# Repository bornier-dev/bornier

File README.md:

# Bornier

Open source EtherCAT slaves for machine tools running LinuxCNC: hardware, firmware and tooling.

- Website: [bornier.dev](https://bornier.dev)

> **Status: board bring-up.** Nothing here is usable yet. The first base boards are built and
> are being brought up block by block: the firmware runs on them and has on-target tests for
> the blocks checked so far, without the EtherCAT stack yet.

## Goals

- A family of standard-compliant EtherCAT slaves for CNC retrofits: motion (step/dir, encoders, probe), digital and analog I/O, spindle control, Modbus gateway.
- Works with any EtherCAT master; developed and tested against LinuxCNC with the IgH master (`lcec`).
- Firmware builds on the LinuxCNC PC itself with a free toolchain (`arm-none-eabi-gcc`, CMake) and updates over EtherCAT (FoE).
- Hardware designed in KiCad, published in full.

Out of scope: functional safety. E-stop and STO stay hardwired.

## Architecture

```
          EtherCAT (daisy chain)
LinuxCNC PC ──► [Base board A] ──► [EtherCAT drive] ──► [Base board B] ──► ...
 (IgH master)        │ HE10 ribbon (local bus, not EtherCAT)
                     ├── I/O module 1
                     └── I/O module n
```

- **One generic base board** per EtherCAT slave. More axes come from more boards on the
  EtherCAT chain (8 axes with two boards, 12 with three).
- **Extension modules** on DIN rail, chained to the base board by HE10 ribbons: slow I/O on SPI
  chips, without an MCU. A base board and its modules form a single modular slave.

## Base board

Schematic and PCB in [`hardware/base/`](hardware/base), generated by script (see below); the PCB is
being placed.

| Block | Content |
|---|---|
| Core | Microchip LAN9253 EtherCAT slave controller (two ports, RJ45 with magnetics), STM32H523 MCU in LQFP-100 over SPI/OCTOSPI, one shared 25 MHz MEMS oscillator |
| Power | 12 V or 24 V logic supply (10.8–30 V): fuse, TVS, reverse polarity protection, bucks to 5 V and 3.3 V; USB micro-B for bench power and DFU flashing |
| Motion | 4 axes, each on a dual RJ45: drive port (differential step/dir, enable, alarm, current-limited supply output) and encoder port (RS-422, TTL or HTL, 5 V or supply voltage); fast probe input |
| Spindle | 0-10 V speed reference, PWM, enable and direction |
| Modbus | Isolated RS-485, switchable termination |
| Safety | E-stop state input (wired, not a safety function), external watchdog on the MCU reset |
| Local bus | HE10 2 × 17 connector to the extension modules: SPI, 12 chip selects, I²C, IRQ, LATCH, OE |

The STM32H523 footprint takes any STM32H5 in LQFP-100 (H523, H533, H562, H563) without a PCB
change. The board is meant to be fed by a dedicated supply in the same cabinet; the
simulation of the input stage and its limits is in [`hardware/base/sim/`](hardware/base/sim/README.md).

The board is 107.5 × 150 mm. It mounts on a DIN rail in a Phoenix Contact UM-BASIC 108 profile
(housing kit UM-BASIC-KIT-B108-L150-7035), resting on the profile walls at the top level, or
screws onto a panel through four M3 holes at the corners, one of them plated to earth the board.
A plated hole takes the Phoenix PE contact, which earths the board to the DIN rail. Every edge
connector sits on a long edge: the profile closes the short ones; the USB jack is vertical.

## Repository layout

| Directory | Contents |
|---|---|
| [`firmware/`](firmware/README.md) | C++23 firmware on the [OpSy](https://github.com/Otatiaro/OpSy) RTOS, generated STM32H523 register headers, board support for the base board, bring-up examples and on-target tests |
| `hardware/lib/` | `kicadgen`, the Python schematic generator and checker (ERC, netlist), and the symbols, footprints and 3D models missing from the KiCad libraries, with their generators |
| `hardware/base/` | Base board: schematic generator (`gen/`), KiCad project (`kicad/`), Gerbers (`fab/`), circuit simulation (`sim/`) |
| [`tools/hil/`](tools/hil/README.md) | Hardware-in-the-loop test scripts |
| `tools/udev/` | udev rules for debug probes on Linux |

The schematic is generated: edit the scripts in `hardware/base/gen/`, then run
`python hardware/base/gen/schematic.py`, which regenerates it and runs the checks. The PCB is edited in
KiCad: after a schematic change, update it from the schematic (Tools > Update PCB from Schematic).

Building, flashing and coding rules: [CONTRIBUTING.md](CONTRIBUTING.md).

## Licensing

| Part | License |
|---|---|
| Hardware (KiCad projects) | [CERN-OHL-W-2.0](LICENSES/CERN-OHL-W-2.0.txt) |
| Firmware and tools | [MPL-2.0](LICENSES/MPL-2.0.txt) |
| Documentation | [CC-BY-4.0](LICENSES/CC-BY-4.0.txt) |

Each file carries an SPDX header naming its license.

## Official builds and forks

Official releases will carry the Bornier EtherCAT Vendor ID. Forks distributing hardware or firmware must use their own Vendor ID.

EtherCAT® is a registered trademark and patented technology, licensed by Beckhoff Automation GmbH, Germany.

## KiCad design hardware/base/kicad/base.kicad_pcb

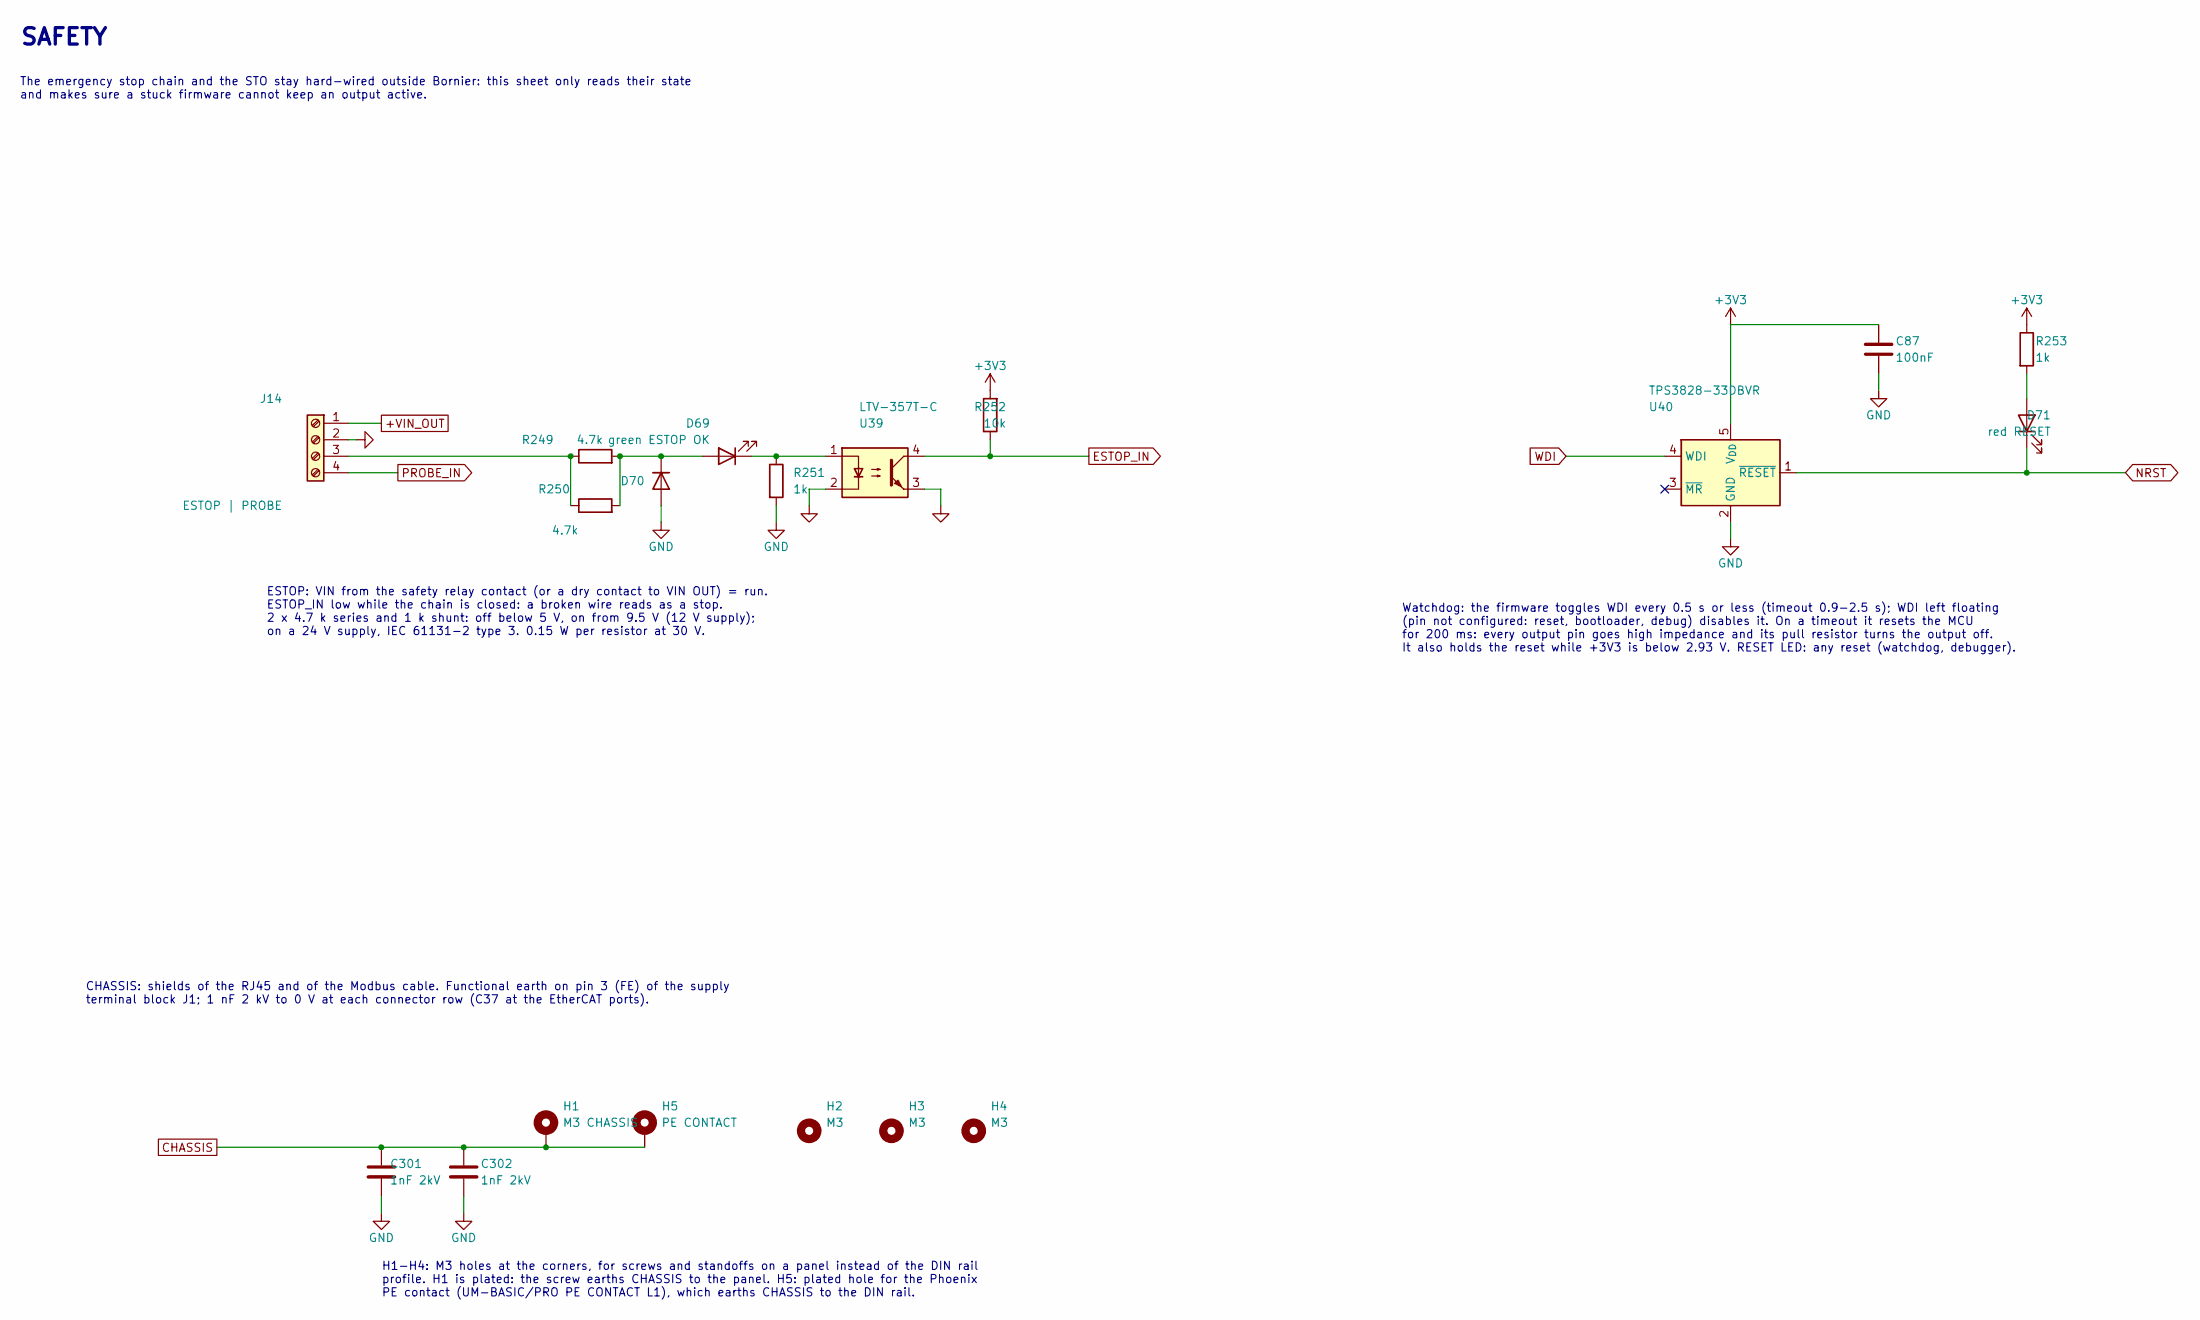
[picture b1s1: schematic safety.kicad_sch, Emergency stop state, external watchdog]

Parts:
C87: 100nF; C_0402_1005Metric; LCSC C307331
C301, C302: 1nF 2kV; C_1206_3216Metric; LCSC C9196
D69: green ESTOP OK; LED_0603_1608Metric; LCSC C2289
D70: 1N4148WS; D_SOD-323; LCSC C2128
D71: red RESET; LED_0603_1608Metric; LCSC C2286
H1: M3 CHASSIS; MountingHole_3.2mm_M3_Pad
H2, H3, H4: M3; MountingHole_3.2mm_M3
H5: PE CONTACT; MountingHole_3.2mm_M3_Pad
J14: ESTOP | PROBE; PhoenixContact_MC_1,5_4-G-3.81_1x04_P3.81mm_Horizontal; LCSC C441184
R249, R250: 4.7k; R_1206_3216Metric; LCSC C17936
R251, R253: 1k; R_0402_1005Metric; LCSC C11702
R252: 10k; R_0402_1005Metric; LCSC C25744
U39: LTV-357T-C; SO-4_4.4x3.6mm_P2.54mm; LCSC C119091
U40: TPS3828-33DBVR; SOT-23-5; LCSC C20032

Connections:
+3V3: C87.1, R252.2, R253.1, U40.5 (V_{DD}); also elsewhere on the board
+VIN_OUT: J14.1; also elsewhere on the board
CHASSIS: C301.1, C302.1, H1.1, H5.1; also elsewhere on the board
ESTOP_IN: R252.1, U39.4; also elsewhere on the board
GND: C87.2, C301.2, C302.2, D70.2 (A), J14.2, R251.2, U39.2, U39.3, U40.2 (GND); also elsewhere on the board
NRST: D71.1 (K), U40.1 (~RESET); also elsewhere on the board
unnamed: D69.2 (A), D70.1 (K), R249.2, R250.2
unnamed: D69.1 (K), R251.1, U39.1
unnamed: D71.2 (A), R253.2
unnamed: J14.3, R249.1, R250.1
PROBE_IN: J14.4; also elsewhere on the board
WDI: U40.4 (WDI); also elsewhere on the board

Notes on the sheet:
SAFETY
The emergency stop chain and the STO stay hard-wired outside Bornier: this sheet only reads their state and makes sure a stuck firmware cannot keep an output active.
ESTOP: VIN from the safety relay contact (or a dry contact to VIN OUT) = run. ESTOP_IN low while the chain is closed: a broken wire reads as a stop. 2 x 4.7 k series and 1 k shunt: off below 5 V, on from 9.5 V (12 V supply); on a 24 V supply, IEC 61131-2 type 3. 0.15 W per resistor at 30 V.
Watchdog: the firmware toggles WDI every 0.5 s or less (timeout 0.9-2.5 s); WDI left floating (pin not configured: reset, bootloader, debug) disables it. On a timeout it resets the MCU for 200 ms: every output pin goes high impedance and its pull resistor turns the output off. It also holds the res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
CHASSIS: shields of the RJ45 and of the Modbus cable. Functional earth on pin 3 (FE) of the supply terminal block J1; 1 nF 2 kV to 0 V at each connector row (C37 at the EtherCAT ports).
H1-H4: M3 holes at the corners, for screws and standoffs on a panel instead of the DIN rail profile. H1 is plated: the screw earths CHASSIS to the panel. H5: plated hole for the Phoenix PE contact (UM-BASIC/PRO PE CONTACT L1), which earths CHASSIS to the DIN rail.

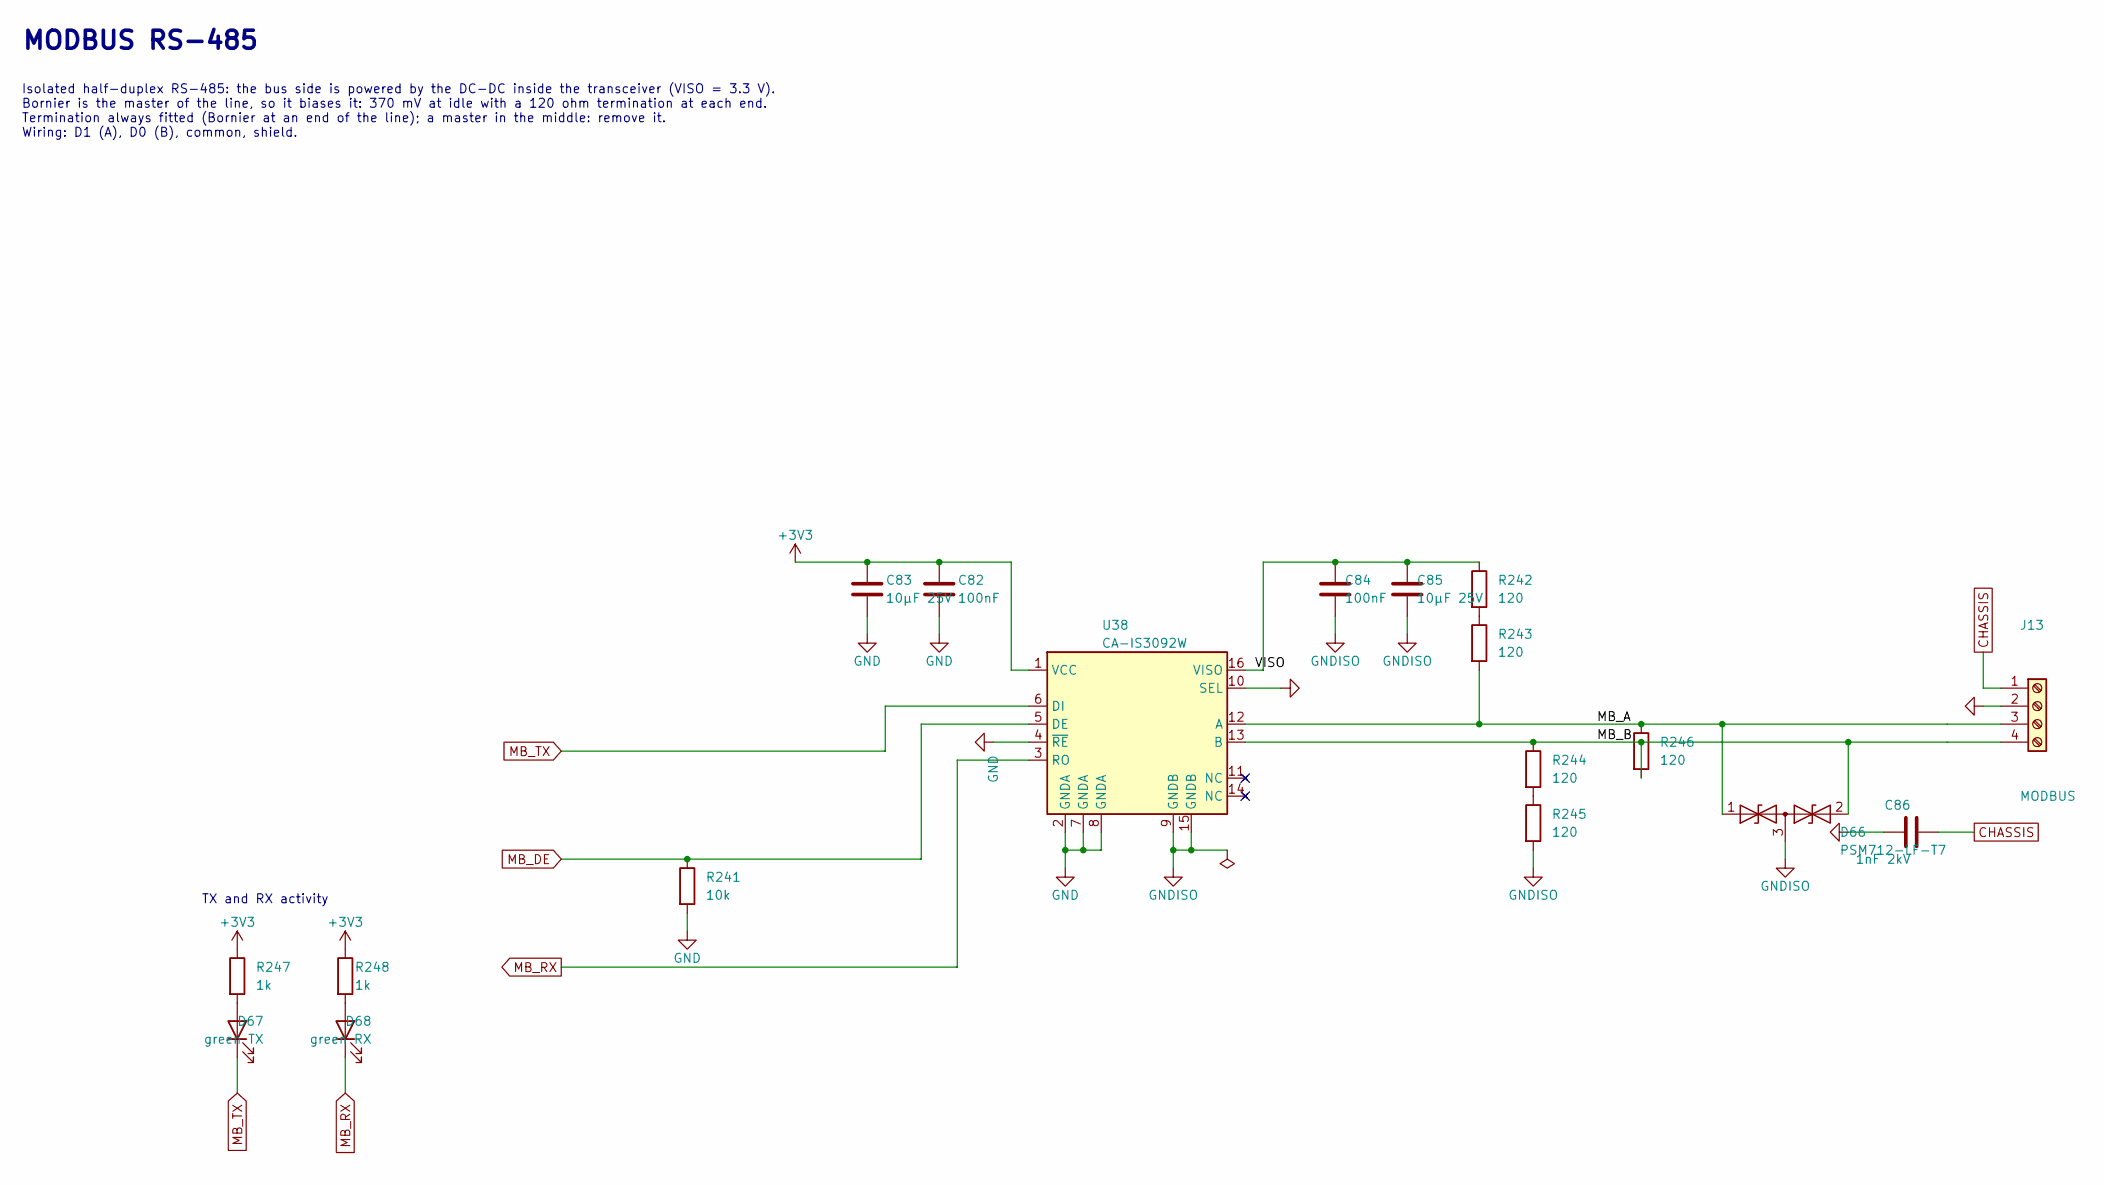
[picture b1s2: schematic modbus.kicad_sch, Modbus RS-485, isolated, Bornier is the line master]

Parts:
C82, C84: 100nF; C_0402_1005Metric; LCSC C307331
C83, C85: 10µF 25V; C_0805_2012Metric; LCSC C15850
C86: 1nF 2kV; C_1206_3216Metric; LCSC C9196
D66: PSM712-LF-T7; SOT-23; LCSC C32677
D67: green TX; LED_0603_1608Metric; LCSC C2289
D68: green RX; LED_0603_1608Metric; LCSC C2289
J13: MODBUS; PhoenixContact_MC_1,5_4-G-3.81_1x04_P3.81mm_Horizontal; LCSC C441184
R241: 10k; R_0402_1005Metric; LCSC C25744
R242, R243, R244, R245, R246: 120; R_0603_1608Metric; LCSC C22787
R247, R248: 1k; R_0402_1005Metric; LCSC C11702
U38: CA-IS3092W; SOIC-16W_7.5x10.3mm_P1.27mm; LCSC C2890051

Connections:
+3V3: C82.1, C83.1, R247.1, R248.1, U38.1 (VCC); also elsewhere on the board
/Modbus/MB_A: D66.1 (A1), J13.3, R243.2, R246.1, U38.12 (A)
/Modbus/MB_B: D66.2 (A2), J13.4, R244.1, R246.2, U38.13 (B)
/Modbus/VISO: C84.1, C85.1, R242.1, U38.16 (VISO)
CHASSIS: C86.2, J13.1; also elsewhere on the board
GND: C82.2, C83.2, R241.2, U38.2 (GNDA), U38.4 (~RE), U38.7 (GNDA), U38.8 (GNDA); also elsewhere on the board
GNDISO: C84.2, C85.2, C86.1, D66.3 (common), J13.2, R245.2, U38.9 (GNDB), U38.10 (SEL), U38.15 (GNDB)
MB_DE: R241.1, U38.5 (DE); also elsewhere on the board
MB_RX: D68.1 (K), U38.3 (RO); also elsewhere on the board
MB_TX: D67.1 (K), U38.6 (DI); also elsewhere on the board
unnamed: D67.2 (A), R247.2
unnamed: D68.2 (A), R248.2
unnamed: R242.2, R243.1
unnamed: R244.2, R245.1

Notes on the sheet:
MODBUS RS-485
Isolated half-duplex RS-485: the bus side is powered by the DC-DC inside the transceiver (VISO = 3.3 V). Bornier is the master of the line, so it biases it: 370 mV at idle with a 120 ohm termination at each end. Termination always fitted (Bornier at an end of the line); a master in the middle: remo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
TX and RX activity

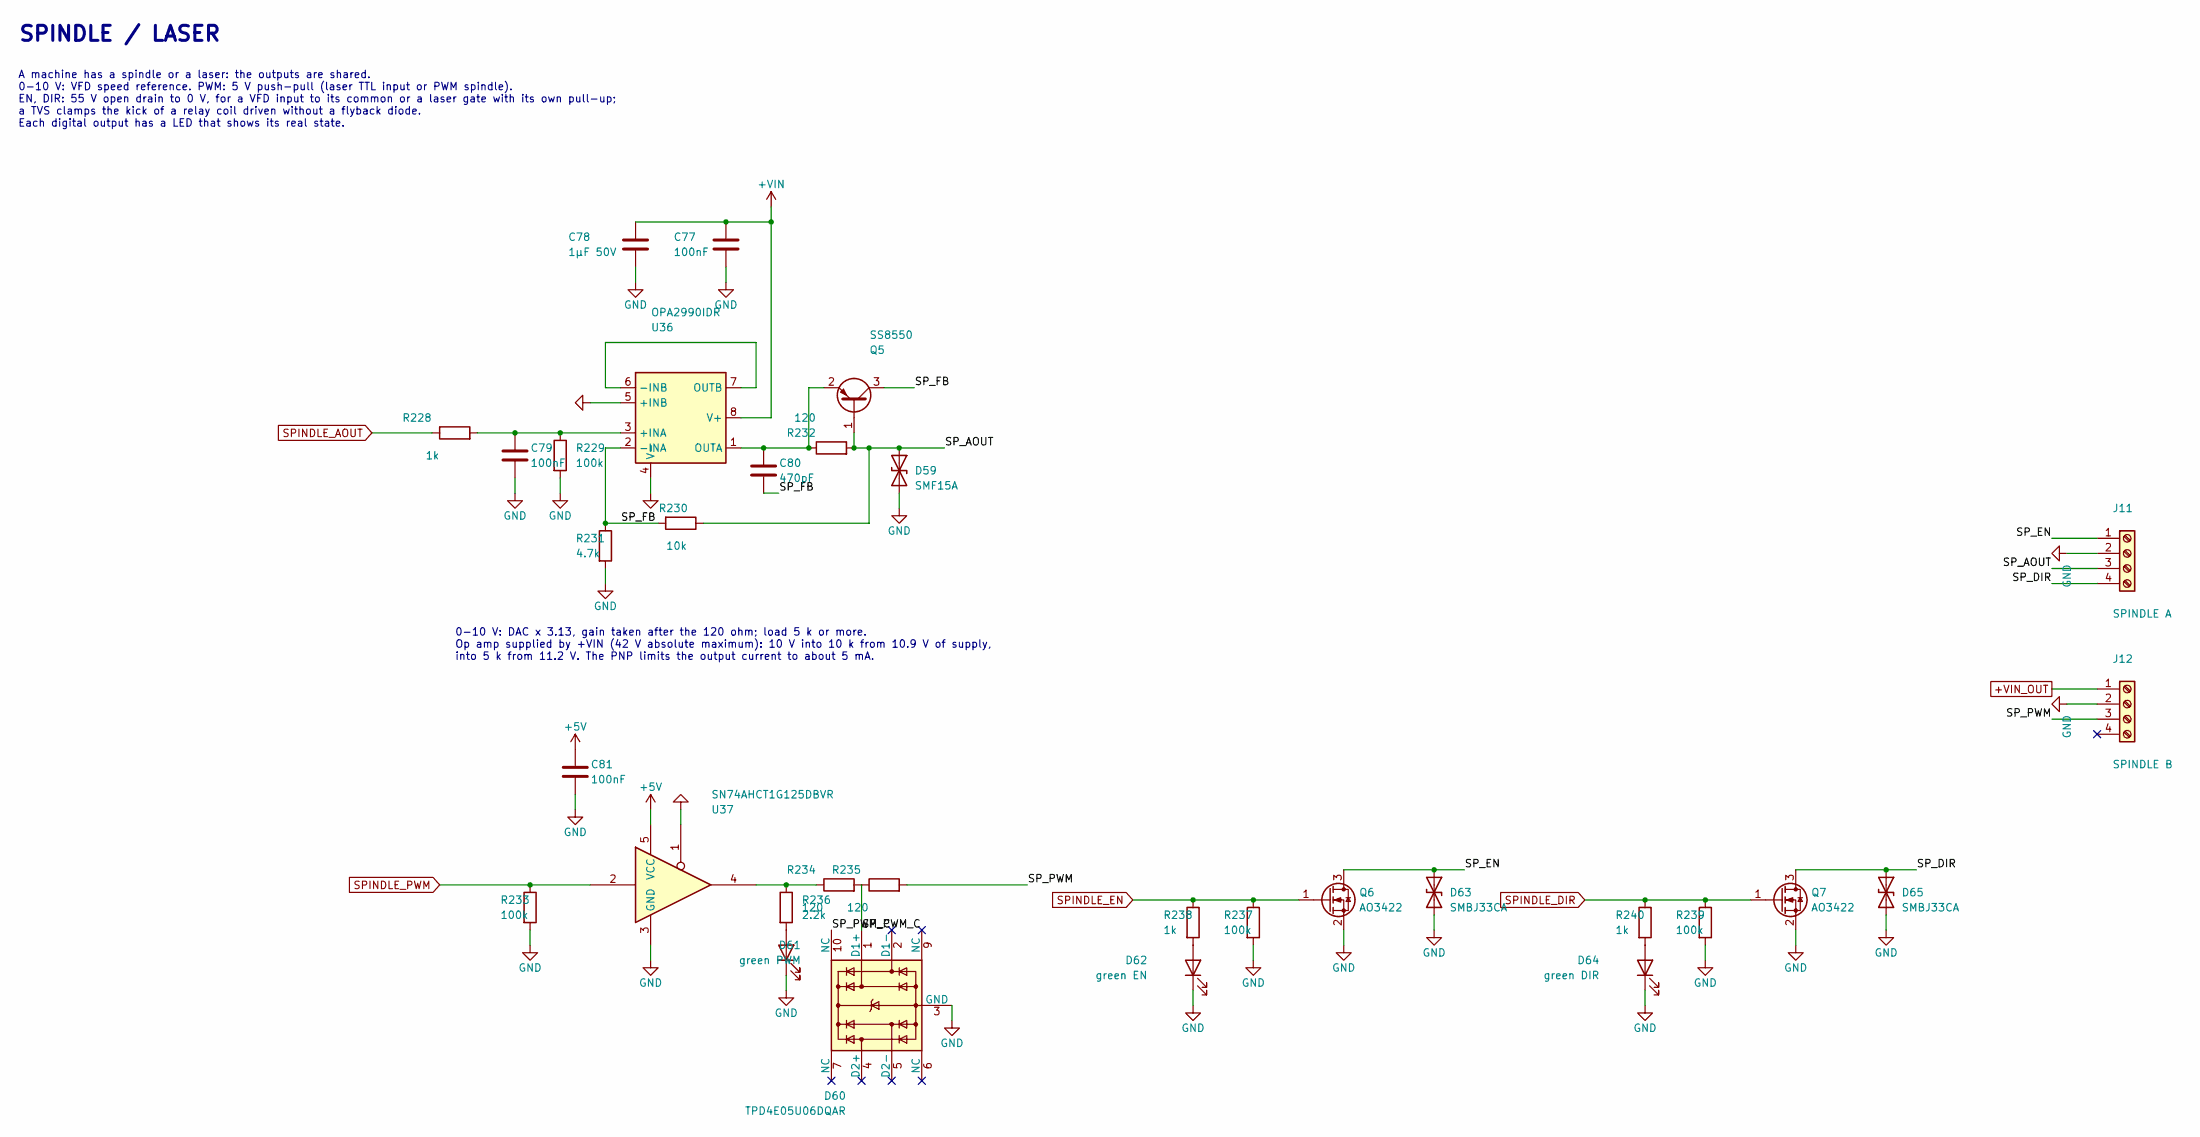
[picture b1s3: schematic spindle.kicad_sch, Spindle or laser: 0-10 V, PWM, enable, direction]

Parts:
C77, C79, C81: 100nF; C_0402_1005Metric; LCSC C307331
C78: 1µF 50V; C_0603_1608Metric; LCSC C15849
C80: 470pF; C_0402_1005Metric; LCSC C1537
D59: SMF15A; D_SOD-123F; LCSC C123802
D60: TPD4E05U06DQAR; USON-10_2.5x1.0mm_P0.5mm; LCSC C138714
D61: green PWM; LED_0603_1608Metric; LCSC C2289
D62: green EN; LED_0603_1608Metric; LCSC C2289
D63, D65: SMBJ33CA; D_SMB; LCSC C78420
D64: green DIR; LED_0603_1608Metric; LCSC C2289
J11: SPINDLE A; PhoenixContact_MC_1,5_4-G-3.81_1x04_P3.81mm_Horizontal; LCSC C441184
J12: SPINDLE B; PhoenixContact_MC_1,5_4-G-3.81_1x04_P3.81mm_Horizontal; LCSC C441184
Q5: SS8550; SOT-23; LCSC C8542
Q6, Q7: AO3422; SOT-23; LCSC C37130
R228, R238, R240: 1k; R_0402_1005Metric; LCSC C11702
R229, R233, R237, R239: 100k; R_0402_1005Metric; LCSC C25741
R230: 10k; R_0402_1005Metric; LCSC C25744
R231: 4.7k; R_0402_1005Metric; LCSC C25900
R232, R234, R235: 120; R_0603_1608Metric; LCSC C22787
R236: 2.2k; R_0402_1005Metric; LCSC C25879
U36: OPA2990IDR; SOIC-8_3.9x4.9mm_P1.27mm; LCSC C2058283
U37: SN74AHCT1G125DBVR; SOT-23-5; LCSC C7484

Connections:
+5V: C81.1, U37.5 (VCC); also elsewhere on the board
+VIN: C77.1, C78.1, U36.8 (V+); also elsewhere on the board
+VIN_OUT: J12.1; also elsewhere on the board
/Spindle/SP_AOUT: D59.1 (A1), J11.3, Q5.1 (B), R230.1, R232.2
/Spindle/SP_DIR: D65.1 (A1), J11.4, Q7.3 (D)
/Spindle/SP_EN: D63.1 (A1), J11.1, Q6.3 (D)
/Spindle/SP_FB: C80.2, Q5.3 (C), R230.2, R231.1, U36.2 (-INA)
/Spindle/SP_PWM: J12.3, R235.2
/Spindle/SP_PWM_C: D60.1 (D1+), D60.10 (NC), R234.2, R235.1
GND: C77.2, C78.2, C79.2, C81.2, D59.2 (A2), D60.3 (GND), D60.8 (GND), D61.1 (K), D62.1 (K), D63.2 (A2), D64.1 (K), D65.2 (A2), J11.2, J12.2, Q6.2 (S), Q7.2 (S), R229.2, R231.2, R233.2, R237.2, R239.2, U36.4 (V-), U36.5 (+INB), U37.1, U37.3 (GND); also elsewhere on the board
unnamed: D61.2 (A), R236.2
unnamed: D62.2 (A), R238.2
unnamed: D64.2 (A), R240.2
unnamed: C80.1, Q5.2 (E), R232.1, U36.1 (OUTA)
unnamed: R234.1, R236.1, U37.4
unnamed: C79.1, R228.2, R229.1, U36.3 (+INA)
unnamed: U36.6 (-INB), U36.7 (OUTB)
SPINDLE_AOUT: R228.1; also elsewhere on the board
SPINDLE_DIR: Q7.1 (G), R239.1, R240.1; also elsewhere on the board
SPINDLE_EN: Q6.1 (G), R237.1, R238.1; also elsewhere on the board
SPINDLE_PWM: R233.1, U37.2; also elsewhere on the board

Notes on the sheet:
SPINDLE / LASER
A machine has a spindle or a laser: the outputs are shared. 0-10 V: VFD speed reference. PWM: 5 V push-pull (laser TTL input or PWM spindle). EN, DIR: 55 V open drain to 0 V, for a VFD input to its common or a laser gate with its own pull-up; a TVS clamps the kick of a relay coil driven without a f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
0-10 V: DAC x 3.13, gain taken after the 120 ohm; load 5 k or more. Op amp supplied by +VIN (42 V absolute maximum): 10 V into 10 k from 10.9 V of supply, into 5 k from 11.2 V. The PNP limits the output current to about 5 mA.

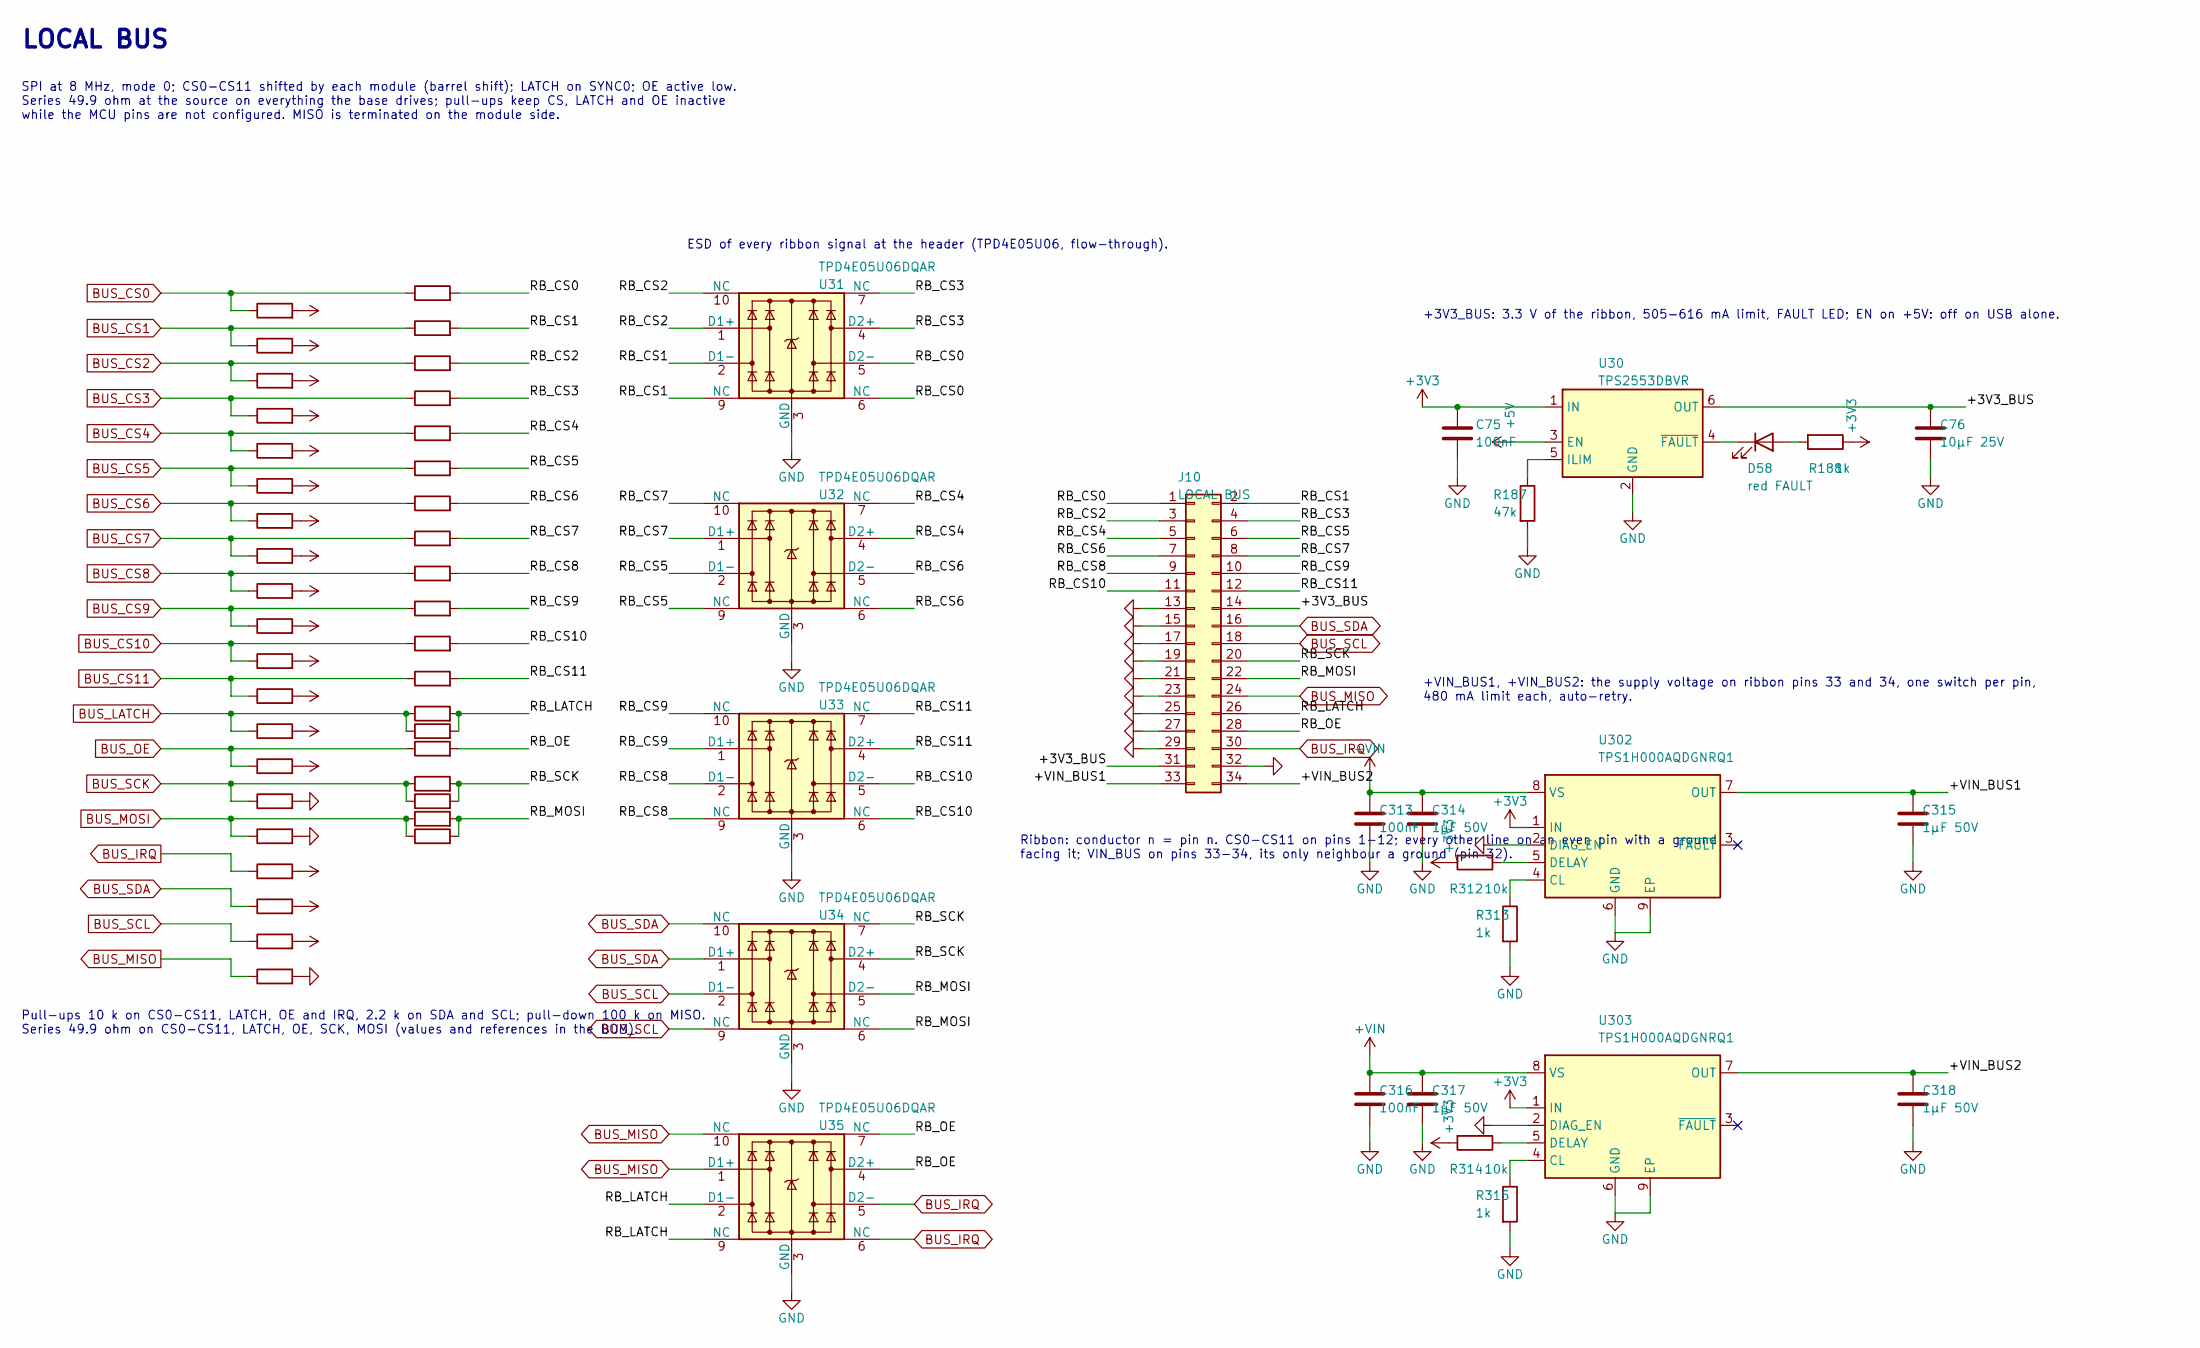
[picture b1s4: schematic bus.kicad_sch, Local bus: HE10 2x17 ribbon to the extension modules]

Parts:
C75, C313, C316: 100nF; C_0402_1005Metric; LCSC C307331
C76: 10µF 25V; C_0805_2012Metric; LCSC C15850
C314, C315, C317, C318: 1µF 50V; C_0603_1608Metric; LCSC C15849
D58: red FAULT; LED_0603_1608Metric; LCSC C2286
J10: LOCAL BUS; IDC-Header_2x17_P2.54mm_Vertical; LCSC C20920
R187: 47k; R_0402_1005Metric; LCSC C25792
R188, R313, R315: 1k; R_0402_1005Metric; LCSC C11702
R189, R190, R191, R192, R193, R194, R195, R196, R197, R198, R199, R200, R201, R202, R222, R312, R314: 10k; R_0402_1005Metric; LCSC C25744
R203, R204, R205, R206, R207, R208, R209, R210, R211, R212, R213, R214, R215, R216, R217, R218, R219, R220, R221: 49.9; R_0603_1608Metric; LCSC C23185
R223, R224, R225: 100k; R_0402_1005Metric; LCSC C25741
R226, R227: 2.2k; R_0402_1005Metric; LCSC C25879
U30: TPS2553DBVR; SOT-23-6; LCSC C55266
U31, U32, U33, U34, U35: TPD4E05U06DQAR; USON-10_2.5x1.0mm_P0.5mm; LCSC C138714
U302, U303: TPS1H000AQDGNRQ1; HVSSOP-8-1EP_3x3mm_P0.65mm_EP1.57x1.89mm; LCSC C2653764

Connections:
+3V3: C75.1, R188.1, R189.2, R190.2, R191.2, R192.2, R193.2, R194.2, R195.2, R196.2, R197.2, R198.2, R199.2, R200.2, R201.2, R202.2, R222.2, R226.2, R227.2, R312.2, R314.2, U30.1 (IN), U302.1 (IN), U303.1 (IN); also elsewhere on the board
+5V: U30.3 (EN); also elsewhere on the board
+VIN: C313.1, C314.1, C316.1, C317.1, U302.8 (VS), U303.8 (VS); also elsewhere on the board
/Local bus/+3V3_BUS: C76.1, J10.14, J10.31, U30.6 (OUT)
/Local bus/+VIN_BUS1: C315.1, J10.33, U302.7 (OUT)
/Local bus/+VIN_BUS2: C318.1, J10.34, U303.7 (OUT)
/Local bus/RB_CS0: J10.1, R203.2, U31.5 (D2-), U31.6 (NC)
/Local bus/RB_CS1: J10.2, R204.2, U31.2 (D1-), U31.9 (NC)
/Local bus/RB_CS2: J10.3, R205.2, U31.1 (D1+), U31.10 (NC)
/Local bus/RB_CS3: J10.4, R206.2, U31.4 (D2+), U31.7 (NC)
/Local bus/RB_CS4: J10.5, R207.2, U32.4 (D2+), U32.7 (NC)
/Local bus/RB_CS5: J10.6, R208.2, U32.2 (D1-), U32.9 (NC)
/Local bus/RB_CS6: J10.7, R209.2, U32.5 (D2-), U32.6 (NC)
/Local bus/RB_CS7: J10.8, R210.2, U32.1 (D1+), U32.10 (NC)
/Local bus/RB_CS8: J10.9, R211.2, U33.2 (D1-), U33.9 (NC)
/Local bus/RB_CS9: J10.10, R212.2, U33.1 (D1+), U33.10 (NC)
/Local bus/RB_CS10: J10.11, R213.2, U33.5 (D2-), U33.6 (NC)
/Local bus/RB_CS11: J10.12, R214.2, U33.4 (D2+), U33.7 (NC)
/Local bus/RB_LATCH: J10.26, R217.2, R221.2, U35.2 (D1-), U35.9 (NC)
/Local bus/RB_MOSI: J10.22, R216.2, R220.2, U34.5 (D2-), U34.6 (NC)
/Local bus/RB_OE: J10.28, R218.2, U35.4 (D2+), U35.7 (NC)
/Local bus/RB_SCK: J10.20, R215.2, R219.2, U34.4 (D2+), U34.7 (NC)
BUS_CS0: R189.1, R203.1; also elsewhere on the board
BUS_CS1: R190.1, R204.1; also elsewhere on the board
BUS_CS2: R191.1, R205.1; also elsewhere on the board
BUS_CS3: R192.1, R206.1; also elsewhere on the board
BUS_CS4: R193.1, R207.1; also elsewhere on the board
BUS_CS5: R194.1, R208.1; also elsewhere on the board
BUS_CS6: R195.1, R209.1; also elsewhere on the board
BUS_CS7: R196.1, R210.1; also elsewhere on the board
BUS_CS8: R197.1, R211.1; also elsewhere on the board
BUS_CS9: R198.1, R212.1; also elsewhere on the board
BUS_CS10: R199.1, R213.1; also elsewhere on the board
BUS_CS11: R200.1, R214.1; also elsewhere on the board
BUS_IRQ: J10.30, R222.1, U35.5 (D2-), U35.6 (NC); also elsewhere on the board
BUS_LATCH: R201.1, R217.1, R221.1; also elsewhere on the board
BUS_MISO: J10.24, R223.1, U35.1 (D1+), U35.10 (NC); also elsewhere on the board
BUS_MOSI: R216.1, R220.1, R225.1; also elsewhere on the board
BUS_OE: R202.1, R218.1; also elsewhere on the board
BUS_SCK: R215.1, R219.1, R224.1; also elsewhere on the board
BUS_SCL: J10.18, R227.1, U34.2 (D1-), U34.9 (NC); also elsewhere on the board
BUS_SDA: J10.16, R226.1, U34.1 (D1+), U34.10 (NC); also elsewhere on the board
GND: C75.2, C76.2, C313.2, C314.2, C315.2, C316.2, C317.2, C318.2, J10.13, J10.15, J10.17, J10.19, J10.21, J10.23, J10.25, J10.27, J10.29, J10.32, R187.2, R223.2, R224.2, R225.2, R313.2, R315.2, U30.2 (GND), U31.3 (GND), U31.8 (GND), U32.3 (GND), U32.8 (GND), U33.3 (GND), U33.8 (GND), U34.3 (GND), U34.8 (GND), U35.3 (GND), U35.8 (GND), U302.2 (DIAG_EN), U302.6 (GND), U302.9 (EP), U303.2 (DIAG_EN), U303.6 (GND), U303.9 (EP); also elsewhere on the board
unnamed: D58.2 (A), R188.2
unnamed: D58.1 (K), U30.4 (~FAULT)
unnamed: R187.1, U30.5 (ILIM)
unnamed: R313.1, U302.4 (CL)
unnamed: R312.1, U302.5 (DELAY)
unnamed: R315.1, U303.4 (CL)
unnamed: R314.1, U303.5 (DELAY)

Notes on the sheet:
LOCAL BUS
SPI at 8 MHz, mode 0; CS0-CS11 shifted by each module (barrel shift); LATCH on SYNC0; OE active low. Series 49.9 ohm at the source on everything the base drives; pull-ups keep CS, LATCH and OE inactive while the MCU pins are not configured. MISO is terminated on the module side.
Pull-ups 10 k on CS0-CS11, LATCH, OE and IRQ, 2.2 k on SDA and SCL; pull-down 100 k on MISO. Series 49.9 ohm on CS0-CS11, LATCH, OE, SCK, MOSI (values and references in the BOM).
Ribbon: conductor n = pin n. CS0-CS11 on pins 1-12; every other line on an even pin with a ground facing it; VIN_BUS on pins 33-34, its only neighbour a ground (pin 32).
ESD of every ribbon signal at the header (TPD4E05U06, flow-through).
+3V3_BUS: 3.3 V of the ribbon, 505-616 mA limit, FAULT LED; EN on +5V: off on USB alone.
+VIN_BUS1, +VIN_BUS2: the supply voltage on ribbon pins 33 and 34, one switch per pin, 480 mA limit each, auto-retry.

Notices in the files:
firmware/boards/base/esc_bus.hpp:
SPDX-License-Identifier: MPL-2.0
SPDX-FileCopyrightText: 2026 Thomas Legrand
hardware/base/gen/spindle.py:
SPDX-License-Identifier: CERN-OHL-W-2.0
